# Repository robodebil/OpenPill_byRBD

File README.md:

# OpenPill_byRBD
STM32F107VCT6 devboard for DIY PCB Transfer. 1 layer, second lay is jumper

In the near future, I will etch the printed circuit board and post the result a bit later.

I know there are some issues; I’ll do my best to fix them.

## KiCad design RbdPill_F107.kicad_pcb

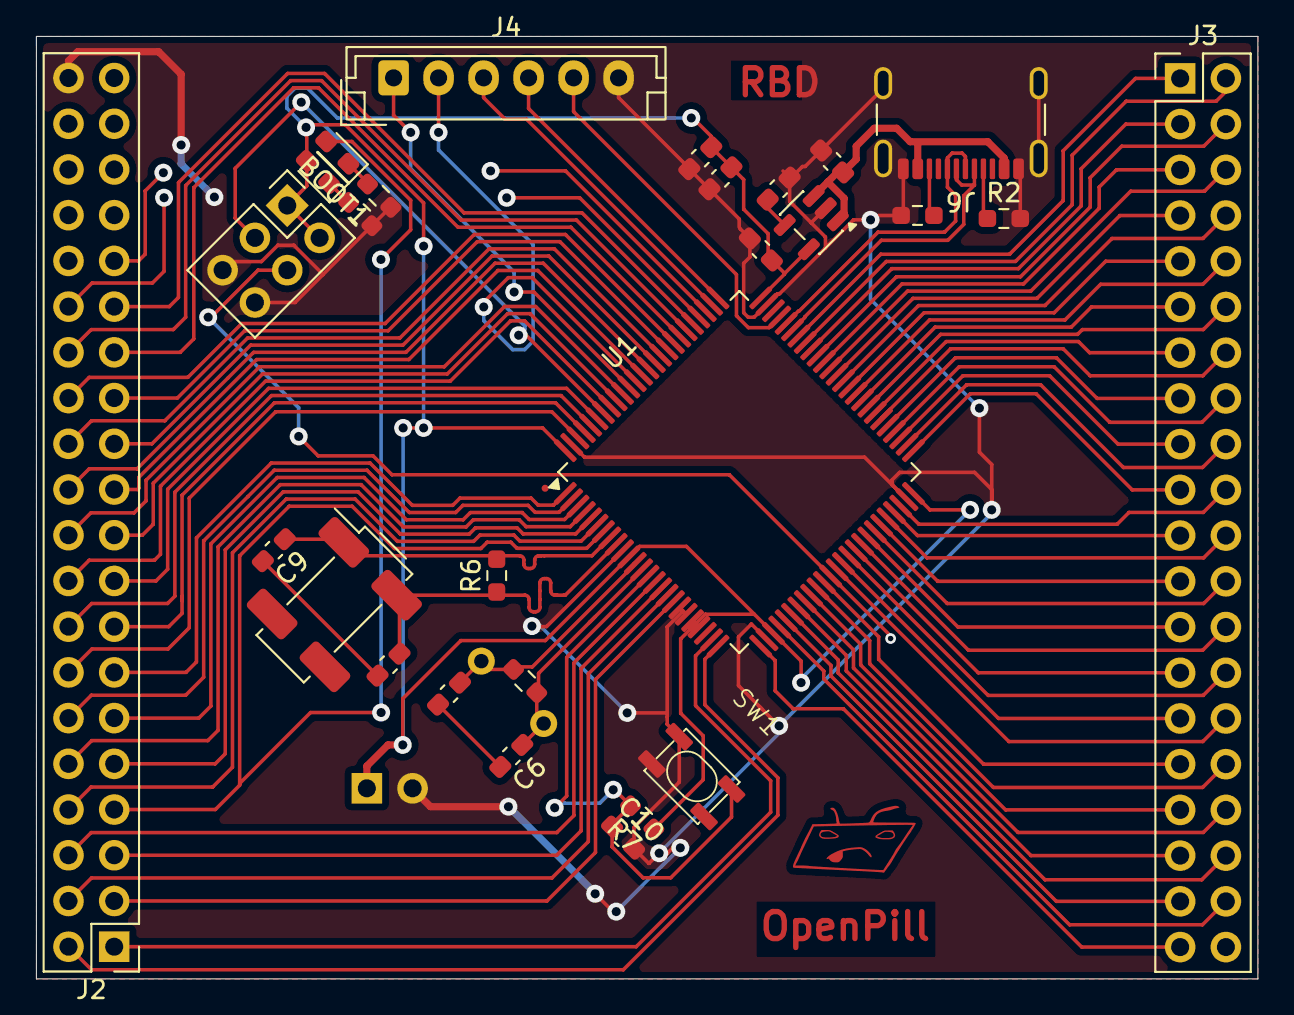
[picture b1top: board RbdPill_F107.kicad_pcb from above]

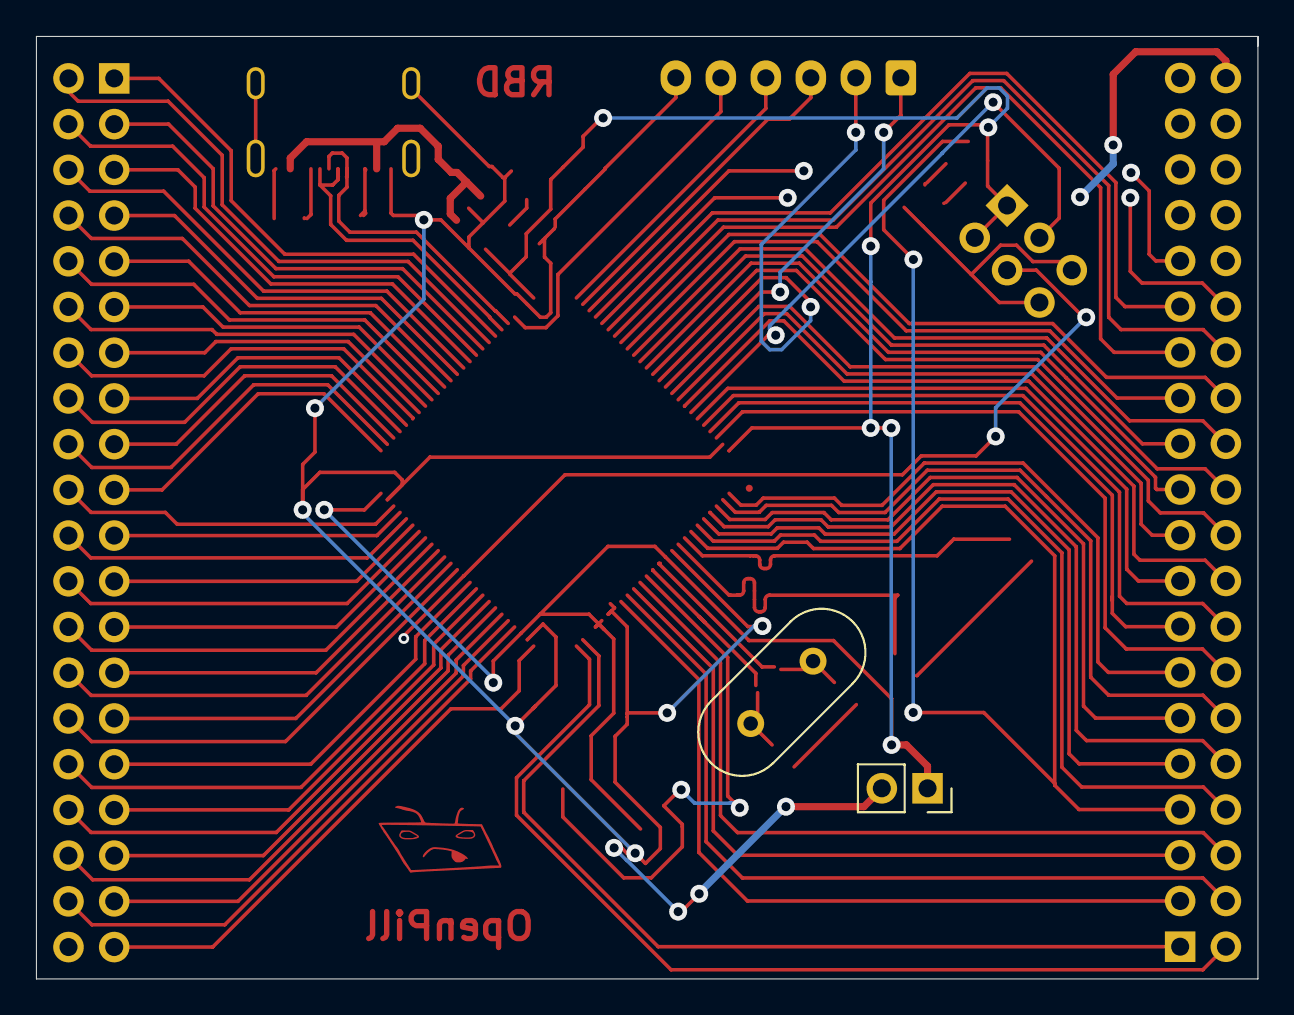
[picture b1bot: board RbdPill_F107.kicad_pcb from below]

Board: 2 copper layers, 67.9 x 52.4 mm, 30 parts (2 on the bottom side), 94 nets.

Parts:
BOOT1: Conn_02x03_Odd_Even; PinHeader_2x03_P2.54mm_Vertical
C1, C2: 1 uF; C_0603_1608Metric_Pad1.08x0.95mm_HandSolder
C3: 10 nF; C_0603_1608Metric_Pad1.08x0.95mm_HandSolder
C4, C5: 100 nF; C_0603_1608Metric_Pad1.08x0.95mm_HandSolder
C6, C7, C8, C9: 40 pF; C_0603_1608Metric_Pad1.08x0.95mm_HandSolder
C10: 0.1 uF; C_0603_1608Metric_Pad1.08x0.95mm_HandSolder
D1, D2: LED; LED_0603_1608Metric_Pad1.05x0.95mm_HandSolder
J1: Conn_01x02; PinSocket_1x02_P2.54mm_Vertical
J2, J3: Conn_02x20_Counter_Clockwise; PinHeader_2x20_P2.54mm_Vertical
J4: Conn_01x06; JST_EH_B6B-EH-A_1x06_P2.50mm_Vertical
J6: USB_C_Receptacle_USB2.0_16P; USB_C_Receptacle_GCT_USB4105-xx-A_16P_TopMnt_Horizontal
R1, R6: 1 MOhm; R_0603_1608Metric_Pad0.98x0.95mm_HandSolder
R2, R3: 5.1 kOhm; R_0603_1608Metric_Pad0.98x0.95mm_HandSolder
R4, R5: 510 Ohm; R_0603_1608Metric_Pad0.98x0.95mm_HandSolder
R7: 10 kOhm; R_0603_1608Metric_Pad0.98x0.95mm_HandSolder
SW1: SW_Push; KLS7-TS3401
U1: STM32F107VCTx; LQFP-100_14x14mm_P0.5mm
U3: LD3985M33R_SOT23; SOT-23-5
Y1: 8 MHz; Crystal_HC18-U_Vertical
Y2: 8 MHz; Crystal_SMD_SeikoEpson_MC306-4Pin_8.0x3.2mm_HandSoldering

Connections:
+3.3V: BOOT1.1, BOOT1.2, C1.1, C4.1, C5.1, D1.2 (A), J1.1, R7.1, U1.11 (VDD), U1.21 (VREF+), U1.22 (VDDA), U1.28 (VDD), U1.50 (VDD), U1.75 (VDD), U1.100 (VDD), U3.5 (VOUT)
/BOOT0: BOOT1.3, U1.94 (BOOT0)
/BOOT1: BOOT1.4, U1.37 (PB2)
/PA1: J2.2, U1.25 (PA2)
/PA2: J2.1, U1.24 (PA1)
/PA3: J3.39, U1.26 (PA3)
/PA4: J3.38, U1.29 (PA4)
/PA5: J3.37, U1.30 (PA5)
/PA6: J3.36, U1.31 (PA6)
/PA7: J3.35, U1.32 (PA7)
/PA8: J3.3, U1.67 (PA8)
/PA9: J3.2, U1.68 (PA9)
/PA10: J3.1, U1.69 (PA10)
/PB0: J3.32, U1.35 (PB0)
/PB1: J3.31, U1.36 (PB1)
/PB5: J2.20, U1.91 (PB5)
/PB6: J2.19, U1.92 (PB6)
/PB7: J2.18, U1.93 (PB7)
/PB8: J2.17, U1.95 (PB8)
/PB9: J2.16, U1.96 (PB9)
/PB10: J3.21, U1.47 (PB10)
/PB11: J3.20, U1.48 (PB11)
/PB12: J3.19, U1.51 (PB12)
/PB13: J3.18, U1.52 (PB13)
/PB14: J3.17, U1.53 (PB14)
/PB15: J3.16, U1.54 (PB15)
/PC0: J2.6, U1.15 (PC0)
/PC1: J2.5, U1.16 (PC1)
/PC2: J2.4, U1.17 (PC2)
/PC3: J2.3, U1.18 (PC3)
/PC4: J3.34, U1.33 (PC4)
/PC6: J3.7, U1.63 (PC6)
/PC7: J3.6, U1.64 (PC7)
/PC8: J3.5, U1.65 (PC8)
/PC9: J3.4, U1.66 (PC9)
/PC10: J2.31, U1.78 (PC10)
/PC11: J2.30, U1.79 (PC11)
/PC12: J2.29, U1.80 (PC12)
/PC13: D2.2 (A), J2.7, U1.7 (PC13)
/PD0: J2.28, U1.81 (PD0)
/PD1: J2.27, U1.82 (PD1)
/PD2: J2.26, U1.83 (PD2)
/PD3: J2.25, U1.84 (PD3)
/PD4: J2.24, U1.85 (PD4)
/PD5: J2.23, U1.86 (PD5)
/PD6: J2.22, U1.87 (PD6)
/PD7: J2.21, U1.88 (PD7)
/PD8: J3.15, U1.55 (PD8)
/PD9: J3.14, U1.56 (PD9)
/PD10: J3.13, U1.57 (PD10)
/PD11: J3.12, U1.58 (PD11)
/PD12: J3.11, U1.59 (PD12)
/PD13: J3.10, U1.60 (PD13)
/PD14: J3.9, U1.61 (PD14)
/PD15: J3.8, U1.62 (PD15)
/PE0: J2.15, U1.97 (PE0)
/PE1: J2.14, U1.98 (PE1)
/PE2: J2.13, U1.1 (PE2)
/PE3: J2.12, U1.2 (PE3)
/PE4: J2.11, U1.3 (PE4)
/PE5: J2.10, U1.4 (PE5)
/PE6: J2.9, U1.5 (PE6)
/PE7: J3.30, U1.38 (PE7)
/PE8: J3.29, U1.39 (PE8)
/PE9: J3.28, U1.40 (PE9)
/PE10: J3.27, U1.41 (PE10)
/PE11: J3.26, U1.42 (PE11)
/PE12: J3.25, U1.43 (PE12)
/PE13: J3.24, U1.44 (PE13)
/PE14: J3.23, U1.45 (PE14)
/PE15: J3.22, U1.46 (PE15)
/PС5: J3.33, U1.34 (PC5)
/RESET: C10.1, R7.2, SW1.2, U1.14 (NRST)
/SYS_CLK: J4.4, U1.76 (PA14)
/SYS_DIO: J4.5, U1.72 (PA13)
/SYS_JTDI: J4.3, U1.77 (PA15)
/SYS_JTDO: J4.2, U1.89 (PB3)
/SYS_NJTRST: J4.1, U1.90 (PB4)
/USB_D+: J6.A6 (D+), J6.B6 (D+), U1.71 (PA12)
/USB_D-: J6.A7 (D-), J6.B7 (D-), U1.70 (PA11)
/VBAT: J2.8, U1.6 (VBAT)
GND: BOOT1.5, BOOT1.6, C1.2, C2.1, C3.1, C4.2, C5.2, C10.2, J1.2, J2.40, J4.6, J6.A1 (GND), J6.A12 (GND), J6.B1 (GND), J6.B12 (GND), J6.SH (SHIELD), R2.2, R3.1, R4.2, R5.2, SW1.1, U1.10 (VSS), U1.19 (VSSA), U1.20 (VREF-), U1.27 (VSS), U1.49 (VSS), U1.74 (VSS), U1.99 (VSS), U3.2 (GND)
unnamed: C6.2, C7.2
unnamed: C8.2, C9.2
unnamed: D1.1 (K), R4.1
unnamed: D2.1 (K), R5.1
unnamed: J6.A5 (CC1), R2.1
unnamed: J6.B5 (CC2), R3.2
unnamed: C7.1, R1.1, U1.12 (OSC_IN), Y1.2
unnamed: C6.1, R1.2, U1.13 (OSC_OUT), Y1.1
unnamed: C9.1, R6.2, U1.8 (PC14), Y2.1
unnamed: C8.1, R6.1, U1.9 (PC15), Y2.2
unnamed: C3.2, U3.4 (BYP)
VCC: C2.2, J6.A4 (VBUS), J6.A9 (VBUS), J6.B4 (VBUS), J6.B9 (VBUS), U3.1 (VIN), U3.3 (INH)
